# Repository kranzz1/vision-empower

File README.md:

# vision-empower
A repository for all things related to the Vision Empower-Stretchable circuits lab project.
Updated for new developments re: CABVI presentation.

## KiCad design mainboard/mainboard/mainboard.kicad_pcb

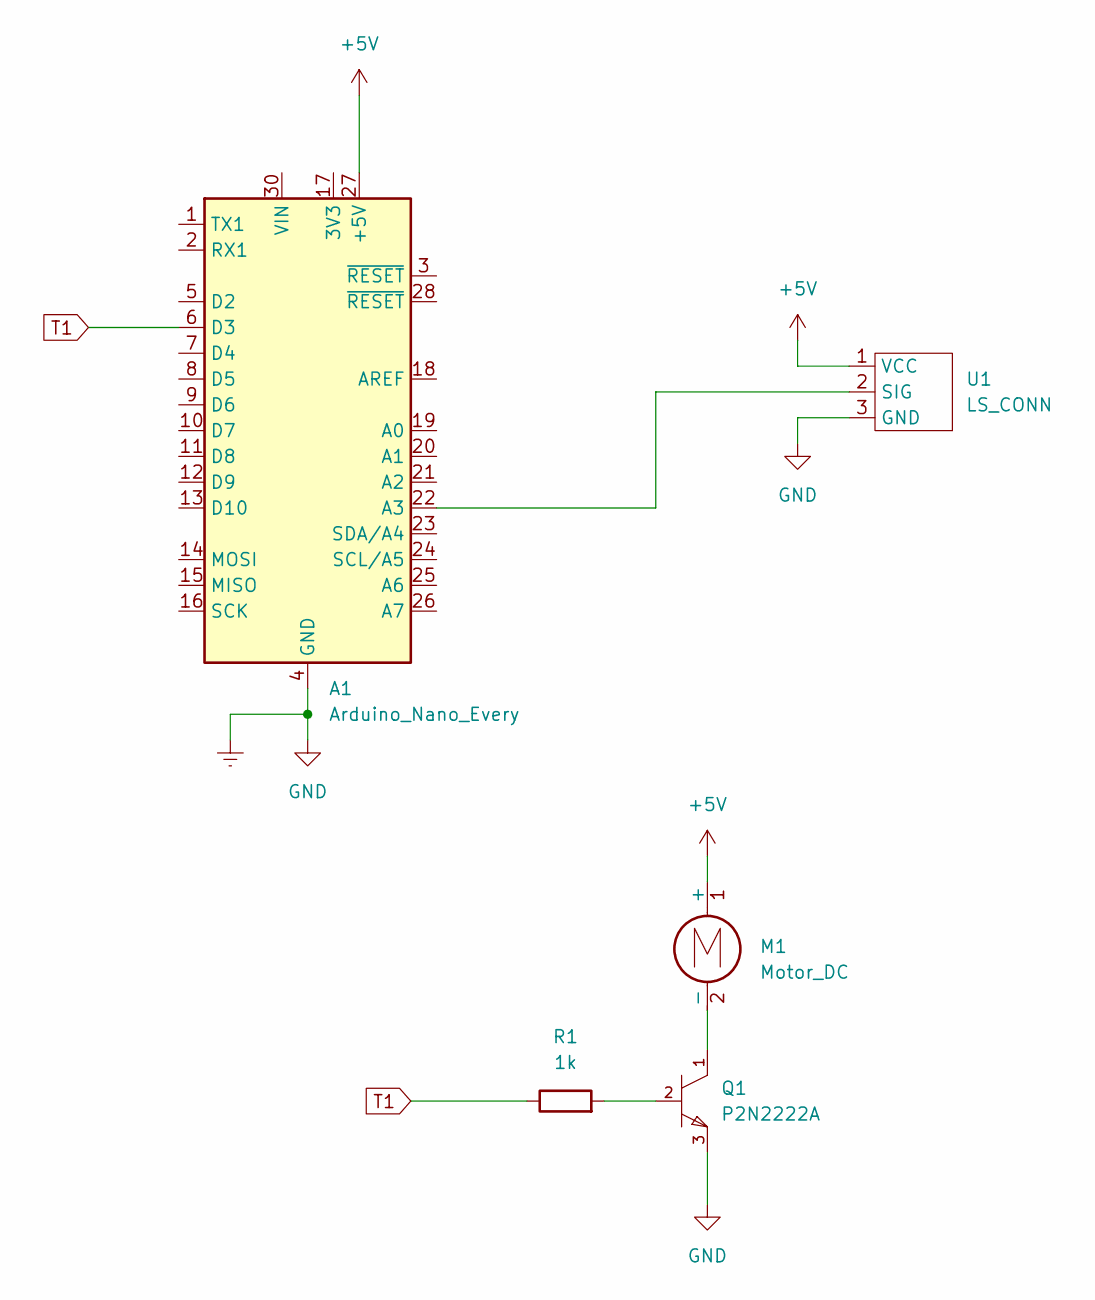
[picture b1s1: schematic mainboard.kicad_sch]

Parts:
A1: Arduino_Nano_Every; Arduino_Nano
M1: Motor_DC; PinHeader_1x02_P1.27mm_Vertical
Q1: P2N2222A; ON_Semi-CASE_2911-0-0-0; mouser part number 863-P2N2222A; digikey description TRANS NPN 40V 0.6A TO92
R1: 1k; R_Axial_DIN0207_L6.3mm_D2.5mm_P7.62mm_Horizontal
U1: LS_CONN; PinHeader_1x03_P1.27mm_Vertical

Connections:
+5V: A1.27 (+5V), M1.1 (+), U1.1 (VCC)
GND: A1.4 (GND), A1.29 (GND), Q1.3 (EMITTER), U1.3 (GND)
unnamed: A1.22 (A3), U1.2 (SIG)
unnamed: M1.2 (-), Q1.1 (COLLECTOR)
unnamed: Q1.2 (BASE), R1.2
T1: A1.6 (D3), R1.1

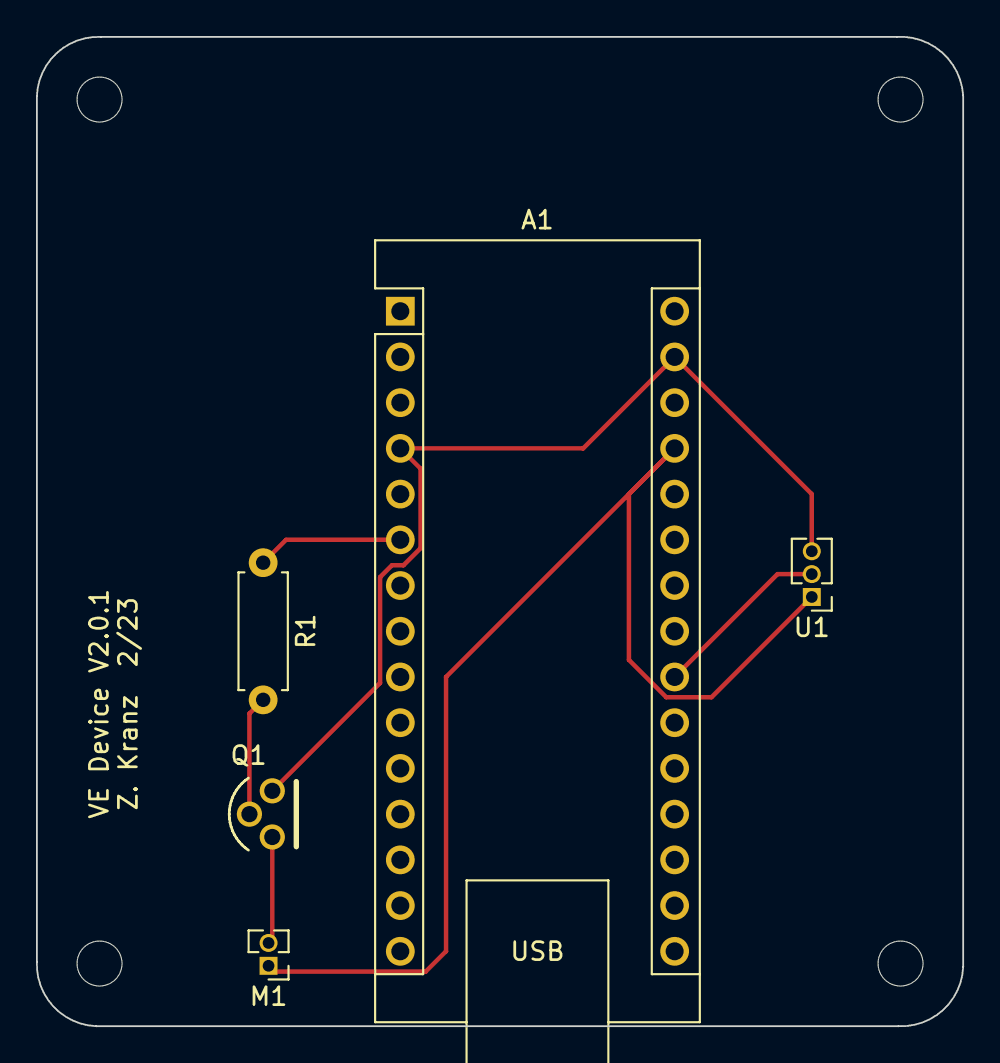
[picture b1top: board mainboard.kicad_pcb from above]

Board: 2 copper layers, 51.5 x 55.0 mm, 5 parts (0 on the bottom side), 6 nets.

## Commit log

2022-03-30 cleaned up code and added comments
2022-03-30 fixed a mistake; code now compiles
2022-03-30 finished code cleanup and comment, added standby
2022-04-06 tested code working 4/6/22
2022-04-06 new version publish
2022-04-12 added binning code
2022-05-20 code fixes for input not working
2022-06-03 Added Case files, updated code
2022-06-03 versioning to 1.5.3
2023-02-15 added kicad files
2023-02-15 added components
2023-02-15 updated symbol/footprint libraries
2023-02-15 library update
2023-02-18 added gerber files
